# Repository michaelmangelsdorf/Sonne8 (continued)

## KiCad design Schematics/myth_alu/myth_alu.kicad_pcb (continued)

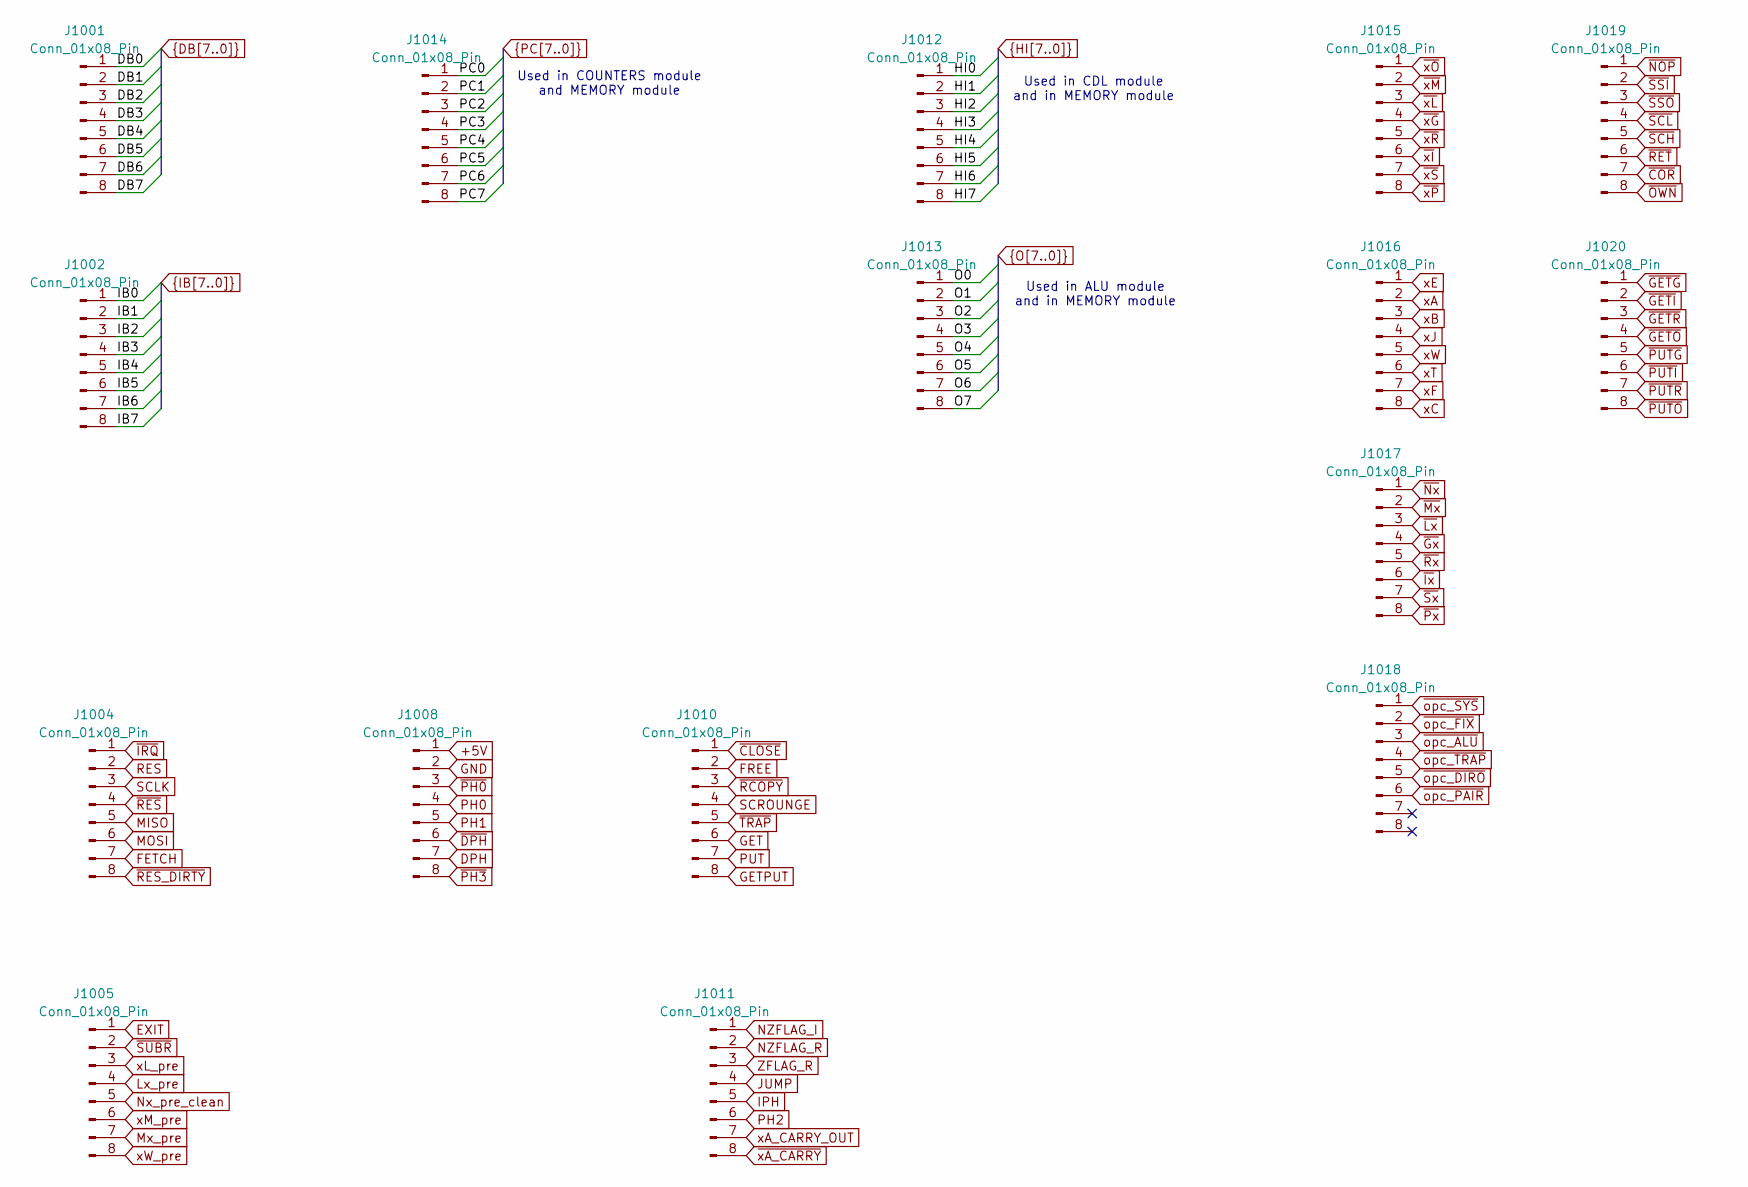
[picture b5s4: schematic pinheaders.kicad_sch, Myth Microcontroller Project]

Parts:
J1001, J1002, J1004, J1005, J1008, J1010, J1011, J1012, J1013, J1014, J1015, J1016, J1017, J1018, J1019, J1020: Conn_01x08_Pin; PinHeader_1x08_P2.54mm_Vertical

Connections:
+5V: J1008.1; also elsewhere on the board
DB0: J1001.1; also elsewhere on the board
DB1: J1001.2; also elsewhere on the board
DB2: J1001.3; also elsewhere on the board
DB3: J1001.4; also elsewhere on the board
DB4: J1001.5; also elsewhere on the board
DB5: J1001.6; also elsewhere on the board
DB6: J1001.7; also elsewhere on the board
DB7: J1001.8; also elsewhere on the board
DPH: J1008.7
EXIT: J1005.1
FETCH: J1004.7
FREE: J1010.2
GET: J1010.6
GETPUT: J1010.8
GND: J1008.2; also elsewhere on the board
HI0: J1012.1
HI1: J1012.2
HI2: J1012.3
HI3: J1012.4
HI4: J1012.5
HI5: J1012.6
HI6: J1012.7
HI7: J1012.8
IB0: J1002.1; also elsewhere on the board
IB1: J1002.2; also elsewhere on the board
IB2: J1002.3; also elsewhere on the board
IB3: J1002.4; also elsewhere on the board
IB4: J1002.5
IB5: J1002.6
IB6: J1002.7
IB7: J1002.8
IPH: J1011.5
JUMP: J1011.4
Lx_pre: J1005.4
MISO: J1004.5
MOSI: J1004.6
Mx_pre: J1005.7
NZFLAG_I: J1011.1
NZFLAG_R: J1011.2; also elsewhere on the board
Nx_pre_clean: J1005.5
O0: J1013.1; also elsewhere on the board
O1: J1013.2; also elsewhere on the board
O2: J1013.3; also elsewhere on the board
O3: J1013.4; also elsewhere on the board
O4: J1013.5; also elsewhere on the board
O5: J1013.6; also elsewhere on the board
O6: J1013.7; also elsewhere on the board
O7: J1013.8; also elsewhere on the board
PC0: J1014.1
PC1: J1014.2
PC2: J1014.3
PC3: J1014.4
PC4: J1014.5
PC5: J1014.6
PC6: J1014.7
PC7: J1014.8
PH0: J1008.4
PH1: J1008.5
PH2: J1011.6
PUT: J1010.7
RES: J1004.2
SCLK: J1004.3
SCROUNGE: J1010.4
ZFLAG_R: J1011.3; also elsewhere on the board
xA: J1016.2; also elsewhere on the board
xA_CARRY_OUT: J1011.7; also elsewhere on the board
xB: J1016.3
xC: J1016.8
xE: J1016.1
xF: J1016.7
xJ: J1016.4
xL_pre: J1005.3
xM_pre: J1005.6
xT: J1016.6
xW: J1016.5
xW_pre: J1005.8
~CLOSE: J1010.1
~COR: J1019.7
~DPH: J1008.6
~Dx: J1017.4
~GETD: J1020.1
~GETI: J1020.2
~GETO: J1020.4
~GETR: J1020.3; also elsewhere on the board
~IRQ: J1004.1
~Ix: J1017.6
~Lx: J1017.3
~Mx: J1017.2
~NOP: J1019.1
~Nx: J1017.1
~OWN: J1019.8
~PH0: J1008.3
~PH3: J1008.8
~PUTD: J1020.5
~PUTI: J1020.6
~PUTO: J1020.8; also elsewhere on the board
~PUTR: J1020.7; also elsewhere on the board
~Px: J1017.8
~RCOPY: J1010.3
~RES_DIRTY: J1004.8
~RES: J1004.4; also elsewhere on the board
~RET: J1019.6
~Rx: J1017.5; also elsewhere on the board
~SCH: J1019.5
~SCL: J1019.4
~SSI: J1019.2
~SSO: J1019.3
~SUBR: J1005.2
~Sx: J1017.7
~TRAP: J1010.5
~opc_ALU: J1018.3; also elsewhere on the board
~opc_DIRO: J1018.5
~opc_FIX: J1018.2; also elsewhere on the board
~opc_PAIR: J1018.6
~opc_SYS: J1018.1
~opc_TRAP: J1018.4
~xA_CARRY: J1011.8
~xD: J1015.4
~xI: J1015.6
~xL: J1015.3
~xM: J1015.2
~xO: J1015.1
~xP: J1015.8
~xR: J1015.5; also elsewhere on the board
~xS: J1015.7

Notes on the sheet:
Used in COUNTERS module and MEMORY module
Used in CDL module and in MEMORY module
Used in ALU module and in MEMORY module

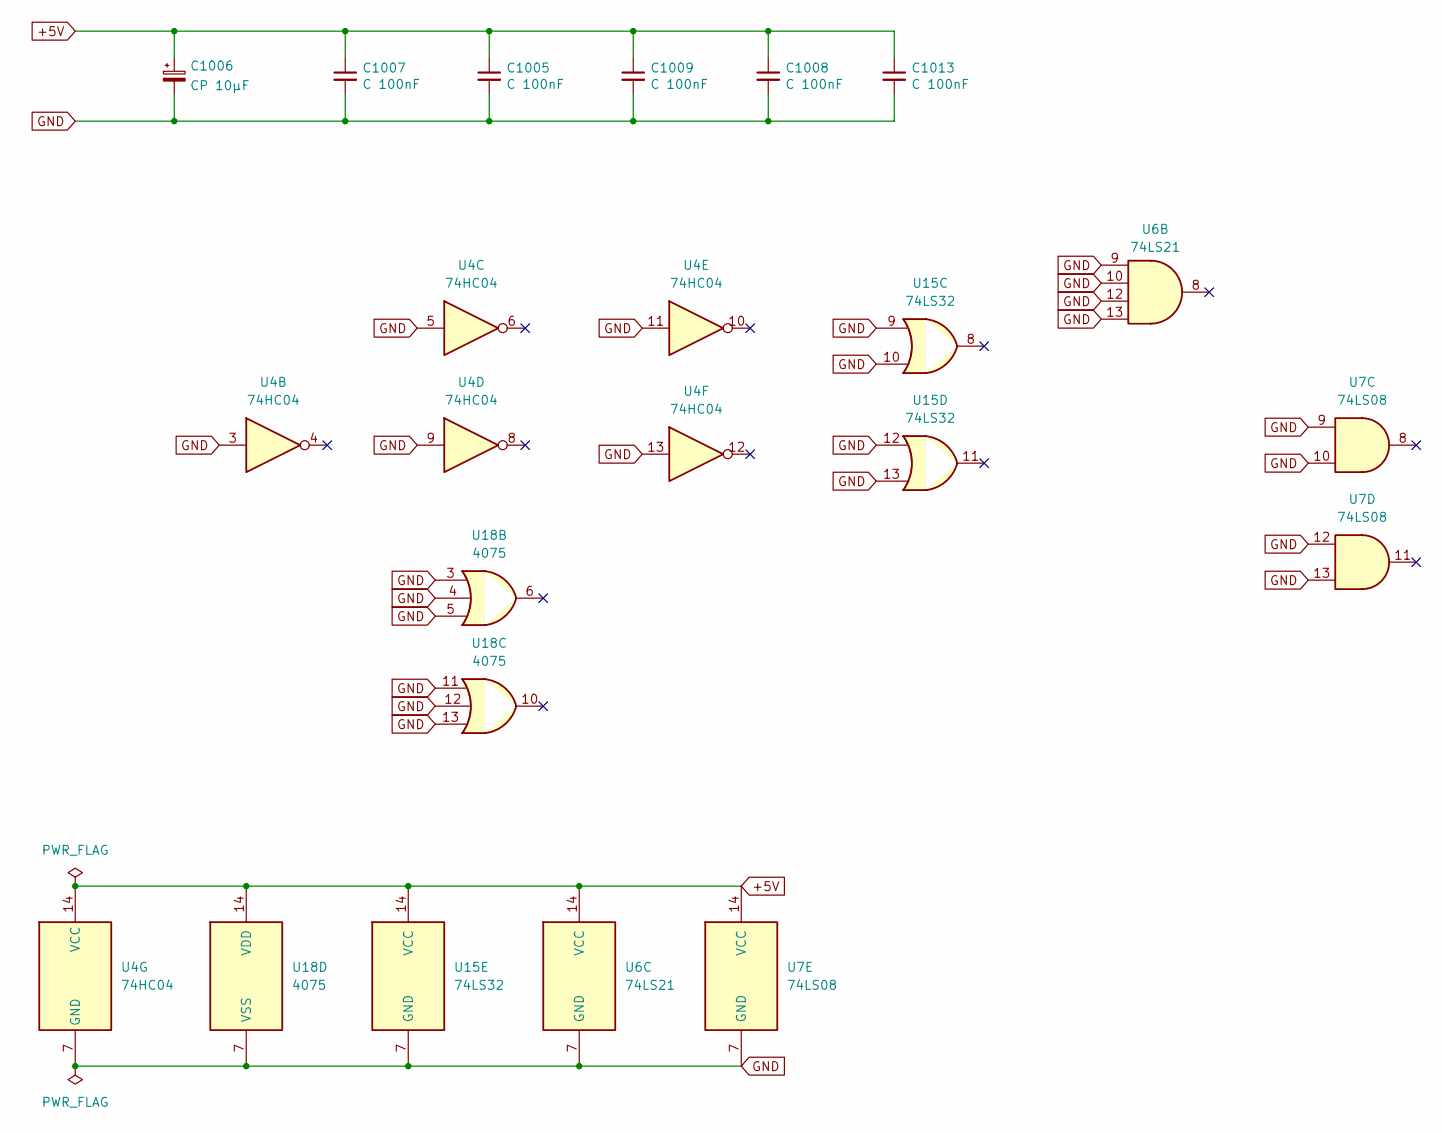
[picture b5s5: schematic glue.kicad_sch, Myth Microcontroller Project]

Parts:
C1005, C1007, C1008, C1009, C1013: C 100nF; C_Disc_D5.0mm_W2.5mm_P2.50mm
C1006: CP 10μF; CP_Radial_D6.3mm_P2.50mm
U4: 74HC04; DIP-14_W7.62mm_Socket_LongPads
U6: 74LS21; DIP-14_W7.62mm_Socket_LongPads
U7: 74LS08; DIP-14_W7.62mm_Socket_LongPads
U15: 74LS32; DIP-14_W7.62mm_Socket_LongPads
U18: 4075; DIP-14_W7.62mm_Socket_LongPads

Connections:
+5V: C1005.1, C1006.1, C1007.1, C1008.1, C1009.1, C1013.1, U4.14 (VCC), U6.14 (VCC), U7.14 (VCC), U15.14 (VCC), U18.14 (VDD); also elsewhere on the board
GND: C1005.2, C1006.2, C1007.2, C1008.2, C1009.2, C1013.2, U4.3, U4.5, U4.7 (GND), U4.9, U4.11, U4.13, U6.7 (GND), U6.9, U6.10, U6.12, U6.13, U7.7 (GND), U7.9, U7.10, U7.12, U7.13, U15.7 (GND), U15.9, U15.10, U15.12, U15.13, U18.3, U18.4, U18.5, U18.7 (VSS), U18.11, U18.12, U18.13; also elsewhere on the board

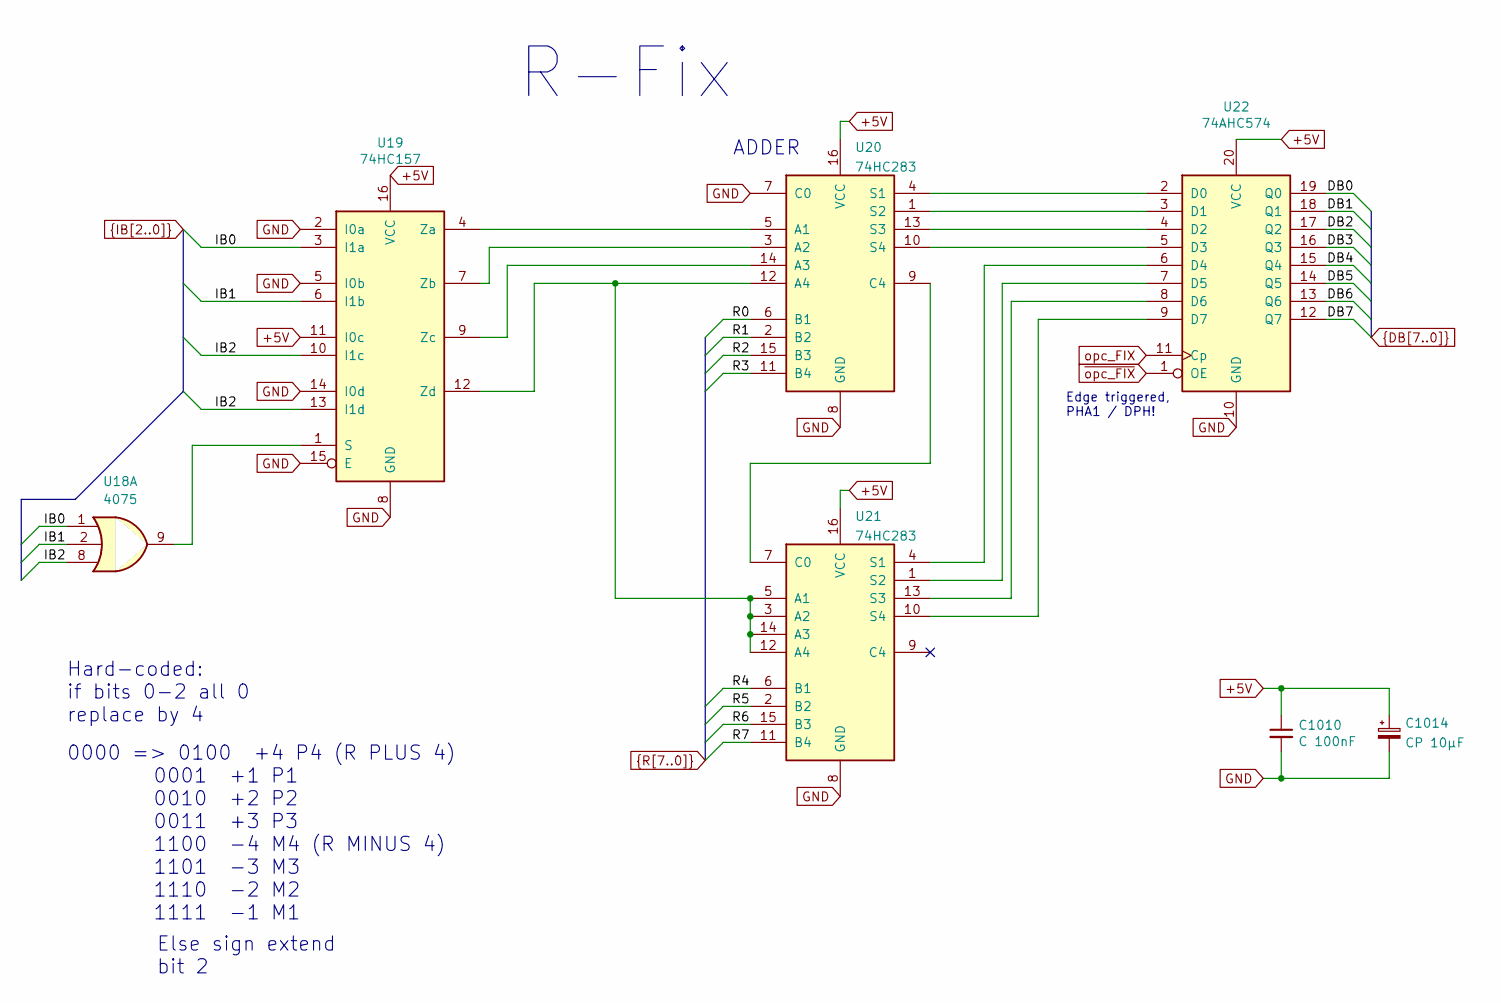
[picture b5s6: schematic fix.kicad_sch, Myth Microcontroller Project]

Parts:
C1010: C 100nF; C_Disc_D5.0mm_W2.5mm_P2.50mm
C1014: CP 10μF; CP_Radial_D6.3mm_P2.50mm
U18: 4075; DIP-14_W7.62mm_Socket_LongPads
U19: 74HC157; DIP-16_W7.62mm_Socket_LongPads
U20, U21: 74HC283; DIP-16_W7.62mm_Socket_LongPads
U22: 74AHC574; DIP-20_W7.62mm_Socket_LongPads

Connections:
+5V: C1010.1, C1014.1, U19.11 (I0c), U19.16 (VCC), U20.16 (VCC), U21.16 (VCC), U22.20 (VCC); also elsewhere on the board
DB0: U22.19 (Q0); also elsewhere on the board
DB1: U22.18 (Q1); also elsewhere on the board
DB2: U22.17 (Q2); also elsewhere on the board
DB3: U22.16 (Q3); also elsewhere on the board
DB4: U22.15 (Q4); also elsewhere on the board
DB5: U22.14 (Q5); also elsewhere on the board
DB6: U22.13 (Q6); also elsewhere on the board
DB7: U22.12 (Q7); also elsewhere on the board
GND: C1010.2, C1014.2, U19.2 (I0a), U19.5 (I0b), U19.8 (GND), U19.14 (I0d), U19.15 (E), U20.7 (C0), U20.8 (GND), U21.8 (GND), U22.10 (GND); also elsewhere on the board
IB0: U18.1, U19.3 (I1a); also elsewhere on the board
IB1: U18.2, U19.6 (I1b); also elsewhere on the board
IB2: U18.8, U19.10 (I1c), U19.13 (I1d); also elsewhere on the board
unnamed: U18.9, U19.1 (S)
unnamed: U19.4 (Za), U20.5 (A1)
unnamed: U19.7 (Zb), U20.3 (A2)
unnamed: U19.9 (Zc), U20.14 (A3)
unnamed: U19.12 (Zd), U20.12 (A4), U21.3 (A2), U21.5 (A1), U21.12 (A4), U21.14 (A3)
unnamed: U20.9 (C4), U21.7 (C0)
unnamed: U20.4 (S1), U22.2 (D0)
unnamed: U20.1 (S2), U22.3 (D1)
unnamed: U20.13 (S3), U22.4 (D2)
unnamed: U20.10 (S4), U22.5 (D3)
unnamed: U21.4 (S1), U22.6 (D4)
unnamed: U21.1 (S2), U22.7 (D5)
unnamed: U21.13 (S3), U22.8 (D6)
unnamed: U21.10 (S4), U22.9 (D7)
R0: U20.6 (B1); also elsewhere on the board
R1: U20.2 (B2); also elsewhere on the board
R2: U20.15 (B3); also elsewhere on the board
R3: U20.11 (B4); also elsewhere on the board
R4: U21.6 (B1); also elsewhere on the board
R5: U21.2 (B2); also elsewhere on the board
R6: U21.15 (B3); also elsewhere on the board
R7: U21.11 (B4); also elsewhere on the board
opc_FIX: U22.11 (Cp)
~opc_FIX: U22.1 (OE); also elsewhere on the board

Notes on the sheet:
ADDER
Edge triggered, PHA1 / DPH!
Else sign extend bit 2
R-Fix
Hard-coded: if bits 0-2 all 0 replace by 4
0000 => 0100 +4 P4 (R PLUS 4) 0001 +1 P1 0010 +2 P2 0011 +3 P3 1100 -4 M4 (R MINUS 4) 1101 -3 M3 1110 -2 M2 1111 -1 M1

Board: 2 copper layers, 52 parts (0 on the bottom side), 96 nets, no tracks yet.

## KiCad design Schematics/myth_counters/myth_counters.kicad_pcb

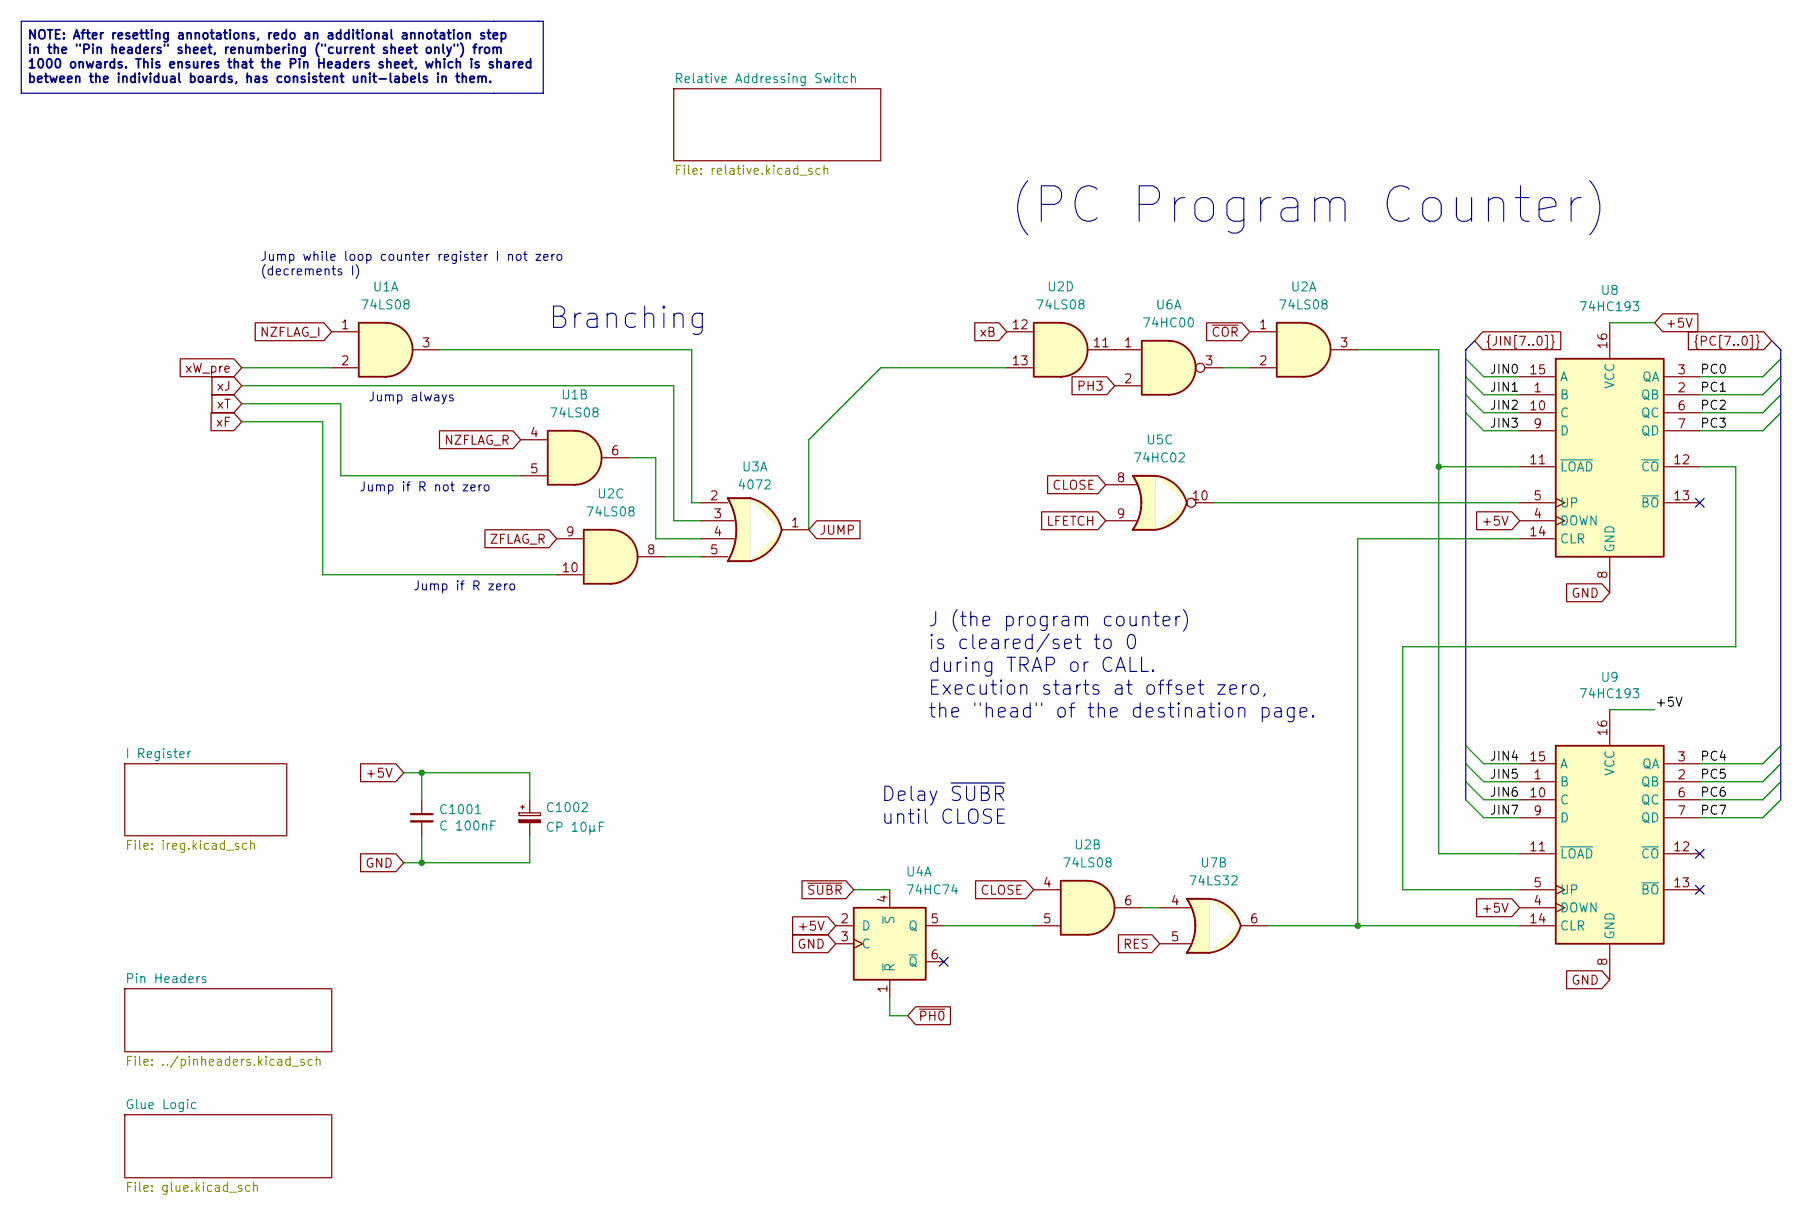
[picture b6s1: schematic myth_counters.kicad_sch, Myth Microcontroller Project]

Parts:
C1001: C 100nF; C_Disc_D5.0mm_W2.5mm_P2.50mm
C1002: CP 10μF; CP_Radial_D6.3mm_P2.50mm
U1, U2: 74LS08; DIP-14_W7.62mm_LongPads
U3: 4072; DIP-14_W7.62mm_LongPads
U4: 74HC74; DIP-14_W7.62mm_LongPads
U5: 74HC02; DIP-14_W7.62mm_LongPads
U6: 74HC00; DIP-14_W7.62mm_LongPads
U7: 74LS32; DIP-14_W7.62mm_LongPads
U8, U9: 74HC193; DIP-16_W7.62mm_Socket_LongPads

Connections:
+5V: C1001.1, C1002.1, U4.2 (D), U8.4 (DOWN), U8.16 (VCC), U9.4 (DOWN), U9.16 (VCC); also elsewhere on the board
CLOSE: U2.4, U5.8
GND: C1001.2, C1002.2, U4.3 (C), U8.8 (GND), U9.8 (GND); also elsewhere on the board
JIN0: U8.15 (A); also elsewhere on the board
JIN1: U8.1 (B); also elsewhere on the board
JIN2: U8.10 (C); also elsewhere on the board
JIN3: U8.9 (D); also elsewhere on the board
JIN4: U9.15 (A); also elsewhere on the board
JIN5: U9.1 (B); also elsewhere on the board
JIN6: U9.10 (C); also elsewhere on the board
JIN7: U9.9 (D); also elsewhere on the board
JUMP: U2.13, U3.1; also elsewhere on the board
LFETCH: U5.9
NZFLAG_I: U1.1; also elsewhere on the board
NZFLAG_R: U1.4; also elsewhere on the board
unnamed: U1.3, U3.2
unnamed: U1.6, U3.4
unnamed: U2.2, U6.3
unnamed: U2.6, U7.4
unnamed: U2.8, U3.5
unnamed: U2.11, U6.1
unnamed: U2.5, U4.5 (Q)
unnamed: U7.6, U8.14 (CLR), U9.14 (CLR)
unnamed: U5.10, U8.5 (UP)
unnamed: U8.12 (~CO), U9.5 (UP)
unnamed: U2.3, U8.11 (~LOAD), U9.11 (~LOAD)
PC0: U8.3 (QA); also elsewhere on the board
PC1: U8.2 (QB); also elsewhere on the board
PC2: U8.6 (QC); also elsewhere on the board
PC3: U8.7 (QD); also elsewhere on the board
PC4: U9.3 (QA); also elsewhere on the board
PC5: U9.2 (QB); also elsewhere on the board
PC6: U9.6 (QC); also elsewhere on the board
PC7: U9.7 (QD); also elsewhere on the board
PH3: U6.2
RES: U7.5; also elsewhere on the board
ZFLAG_R: U2.9; also elsewhere on the board
xB: U2.12; also elsewhere on the board
xF: U2.10; also elsewhere on the board
xJ: U3.3; also elsewhere on the board
xT: U1.5; also elsewhere on the board
xW_pre: U1.2; also elsewhere on the board
~COR: U2.1; also elsewhere on the board
~PH0: U4.1 (~R); also elsewhere on the board
~SUBR: U4.4 (~S); also elsewhere on the board

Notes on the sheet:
Jump always
(PC Program Counter)
Branching
Jump if R zero
J (the program counter) is cleared/set to 0 during TRAP or CALL. Execution starts at offset zero, the "head" of the destination page.
NOTE: After resetting annotations, redo an additional annotation step in the "Pin headers" sheet, renumbering ("current sheet only") from 1000 onwards. This ensures that the Pin Headers sheet, which is shared between the individual boards, has consistent unit-labels in them.
Delay ~{SUBR} until CLOSE
Jump if R not zero
Jump while loop counter register I not zero (decrements I)

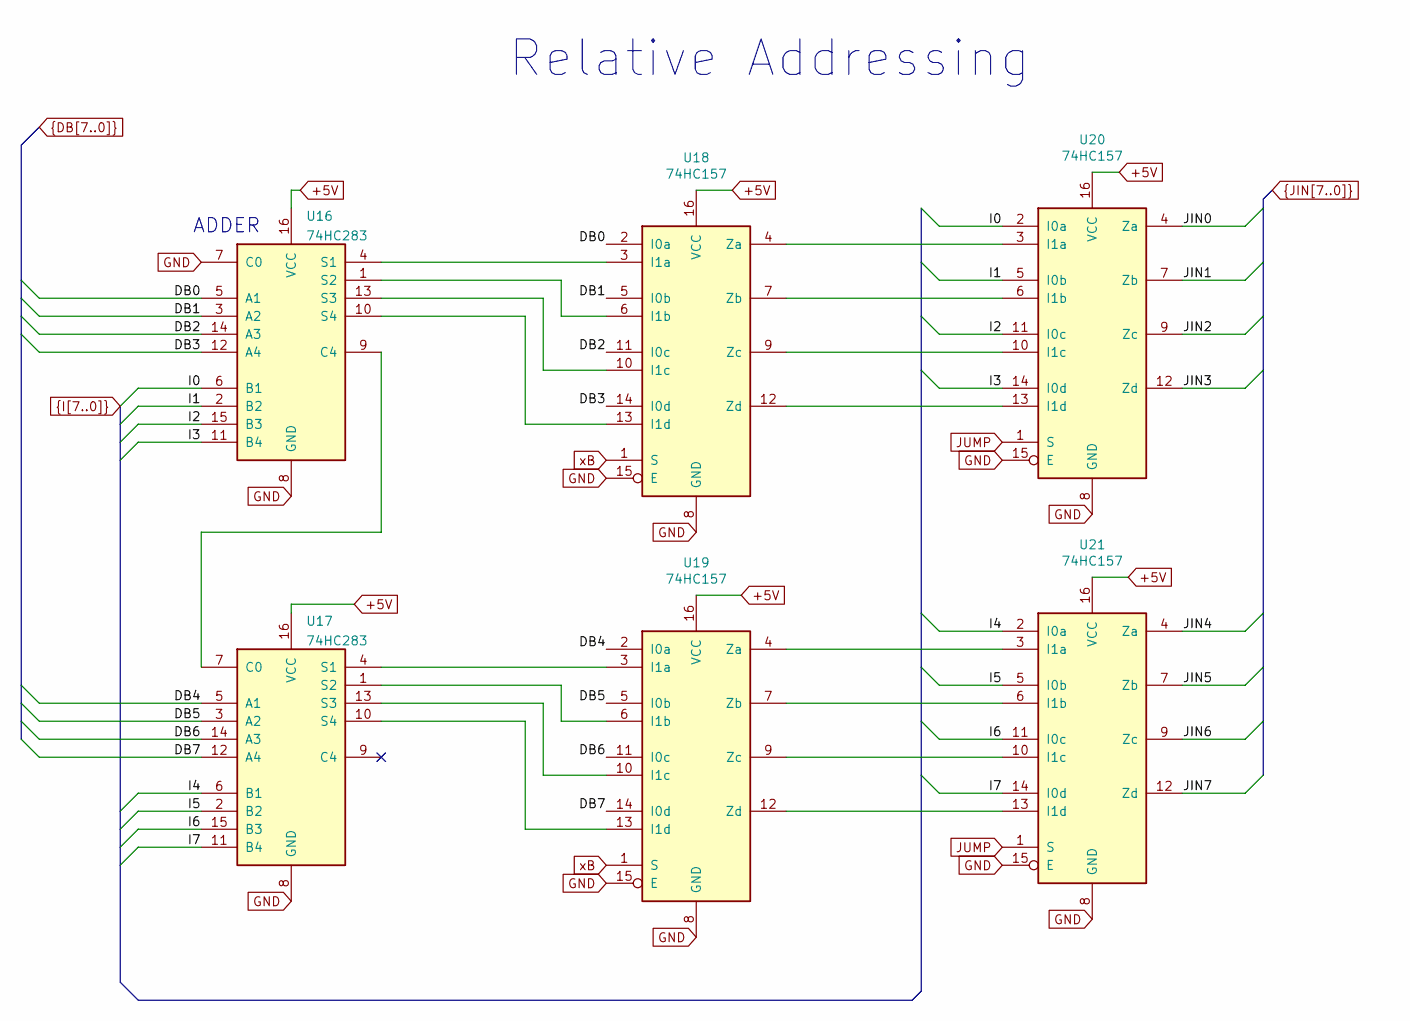
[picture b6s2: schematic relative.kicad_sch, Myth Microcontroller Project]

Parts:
U16, U17: 74HC283; DIP-16_W7.62mm_Socket_LongPads
U18, U19, U20, U21: 74HC157; DIP-16_W7.62mm_Socket_LongPads

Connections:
+5V: U16.16 (VCC), U17.16 (VCC), U18.16 (VCC), U19.16 (VCC), U20.16 (VCC), U21.16 (VCC); also elsewhere on the board
DB0: U16.5 (A1), U18.2 (I0a); also elsewhere on the board
DB1: U16.3 (A2), U18.5 (I0b); also elsewhere on the board
DB2: U16.14 (A3), U18.11 (I0c); also elsewhere on the board
DB3: U16.12 (A4), U18.14 (I0d); also elsewhere on the board
DB4: U17.5 (A1), U19.2 (I0a); also elsewhere on the board
DB5: U17.3 (A2), U19.5 (I0b); also elsewhere on the board
DB6: U17.14 (A3), U19.11 (I0c); also elsewhere on the board
DB7: U17.12 (A4), U19.14 (I0d); also elsewhere on the board
GND: U16.7 (C0), U16.8 (GND), U17.8 (GND), U18.8 (GND), U18.15 (E), U19.8 (GND), U19.15 (E), U20.8 (GND), U20.15 (E), U21.8 (GND), U21.15 (E); also elsewhere on the board
I0: U16.6 (B1), U20.2 (I0a); also elsewhere on the board
I1: U16.2 (B2), U20.5 (I0b); also elsewhere on the board
I2: U16.15 (B3), U20.11 (I0c); also elsewhere on the board
I3: U16.11 (B4), U20.14 (I0d); also elsewhere on the board
I4: U17.6 (B1), U21.2 (I0a); also elsewhere on the board
I5: U17.2 (B2), U21.5 (I0b); also elsewhere on the board
I6: U17.15 (B3), U21.11 (I0c); also elsewhere on the board
I7: U17.11 (B4), U21.14 (I0d); also elsewhere on the board
JIN0: U20.4 (Za); also elsewhere on the board
JIN1: U20.7 (Zb); also elsewhere on the board
JIN2: U20.9 (Zc); also elsewhere on the board
JIN3: U20.12 (Zd); also elsewhere on the board
JIN4: U21.4 (Za); also elsewhere on the board
JIN5: U21.7 (Zb); also elsewhere on the board
JIN6: U21.9 (Zc); also elsewhere on the board
JIN7: U21.12 (Zd); also elsewhere on the board
JUMP: U20.1 (S), U21.1 (S); also elsewhere on the board
unnamed: U16.9 (C4), U17.7 (C0)
unnamed: U16.4 (S1), U18.3 (I1a)
unnamed: U16.1 (S2), U18.6 (I1b)
unnamed: U16.13 (S3), U18.10 (I1c)
unnamed: U16.10 (S4), U18.13 (I1d)
unnamed: U17.4 (S1), U19.3 (I1a)
unnamed: U17.1 (S2), U19.6 (I1b)
unnamed: U17.13 (S3), U19.10 (I1c)
unnamed: U17.10 (S4), U19.13 (I1d)
unnamed: U18.4 (Za), U20.3 (I1a)
unnamed: U18.7 (Zb), U20.6 (I1b)
unnamed: U18.9 (Zc), U20.10 (I1c)
unnamed: U18.12 (Zd), U20.13 (I1d)
unnamed: U19.4 (Za), U21.3 (I1a)
unnamed: U19.7 (Zb), U21.6 (I1b)
unnamed: U19.9 (Zc), U21.10 (I1c)
unnamed: U19.12 (Zd), U21.13 (I1d)
xB: U18.1 (S), U19.1 (S); also elsewhere on the board

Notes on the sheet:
Relative Addressing
ADDER

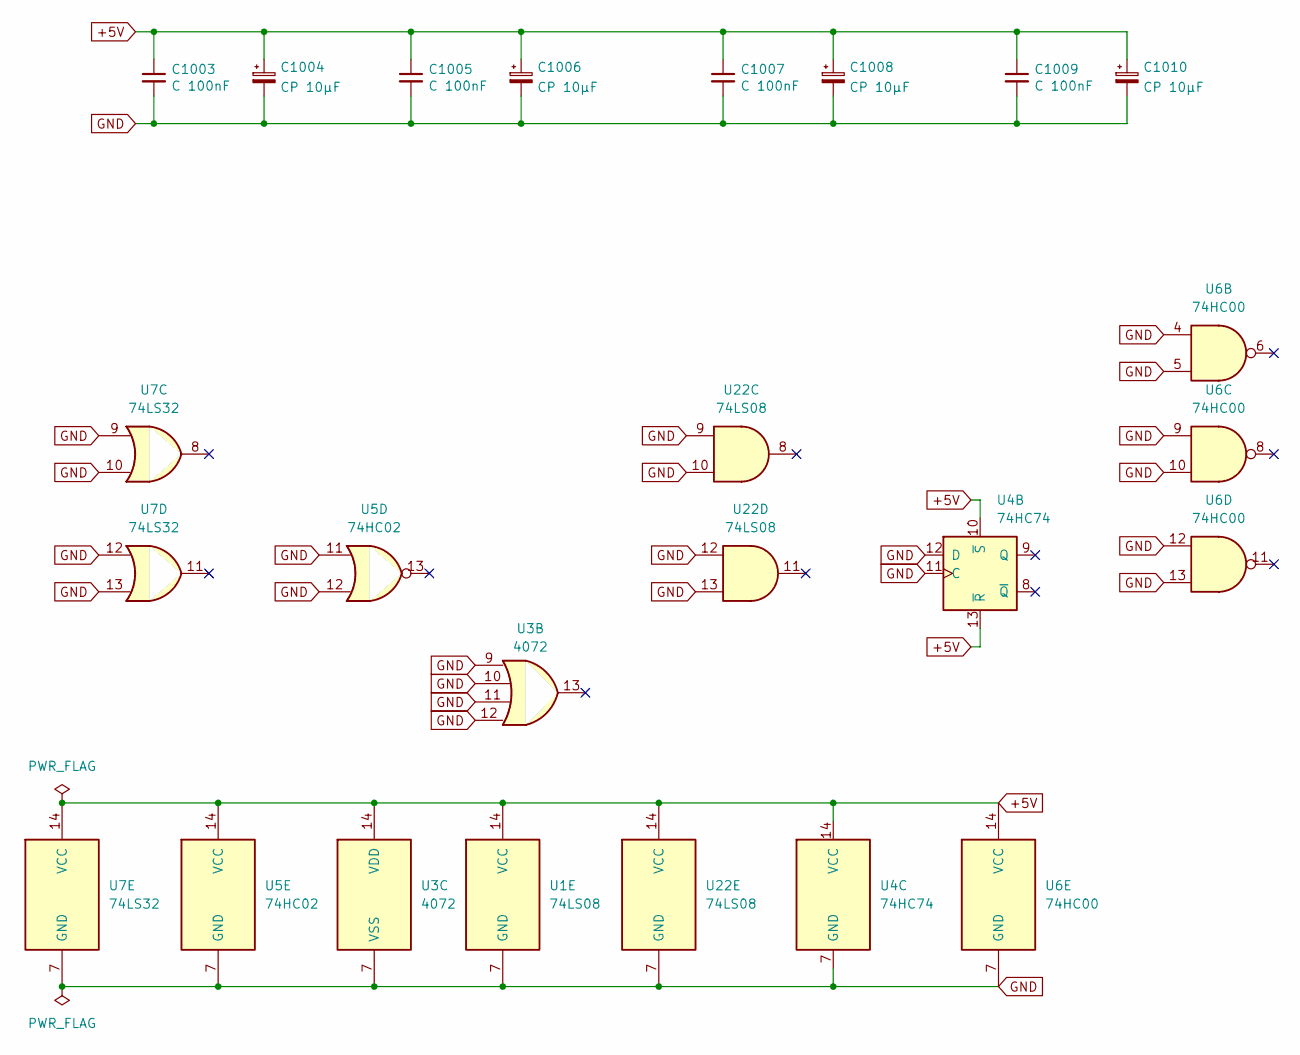
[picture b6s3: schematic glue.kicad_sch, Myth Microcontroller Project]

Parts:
C1003, C1005, C1007, C1009: C 100nF; C_Disc_D5.0mm_W2.5mm_P2.50mm
C1004, C1006, C1008, C1010: CP 10μF; CP_Radial_D6.3mm_P2.50mm
U1, U22: 74LS08; DIP-14_W7.62mm_LongPads
U3: 4072; DIP-14_W7.62mm_LongPads
U4: 74HC74; DIP-14_W7.62mm_LongPads
U5: 74HC02; DIP-14_W7.62mm_LongPads
U6: 74HC00; DIP-14_W7.62mm_LongPads
U7: 74LS32; DIP-14_W7.62mm_LongPads

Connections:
+5V: C1003.1, C1004.1, C1005.1, C1006.1, C1007.1, C1008.1, C1009.1, C1010.1, U1.14 (VCC), U3.14 (VDD), U4.10 (~S), U4.13 (~R), U4.14 (VCC), U5.14 (VCC), U6.14 (VCC), U7.14 (VCC), U22.14 (VCC); also elsewhere on the board
GND: C1003.2, C1004.2, C1005.2, C1006.2, C1007.2, C1008.2, C1009.2, C1010.2, U1.7 (GND), U3.7 (VSS), U3.9, U3.10, U3.11, U3.12, U4.7 (GND), U4.11 (C), U4.12 (D), U5.7 (GND), U5.11, U5.12, U6.4, U6.5, U6.7 (GND), U6.9, U6.10, U6.12, U6.13, U7.7 (GND), U7.9, U7.10, U7.12, U7.13, U22.7 (GND), U22.9, U22.10, U22.12, U22.13; also elsewhere on the board

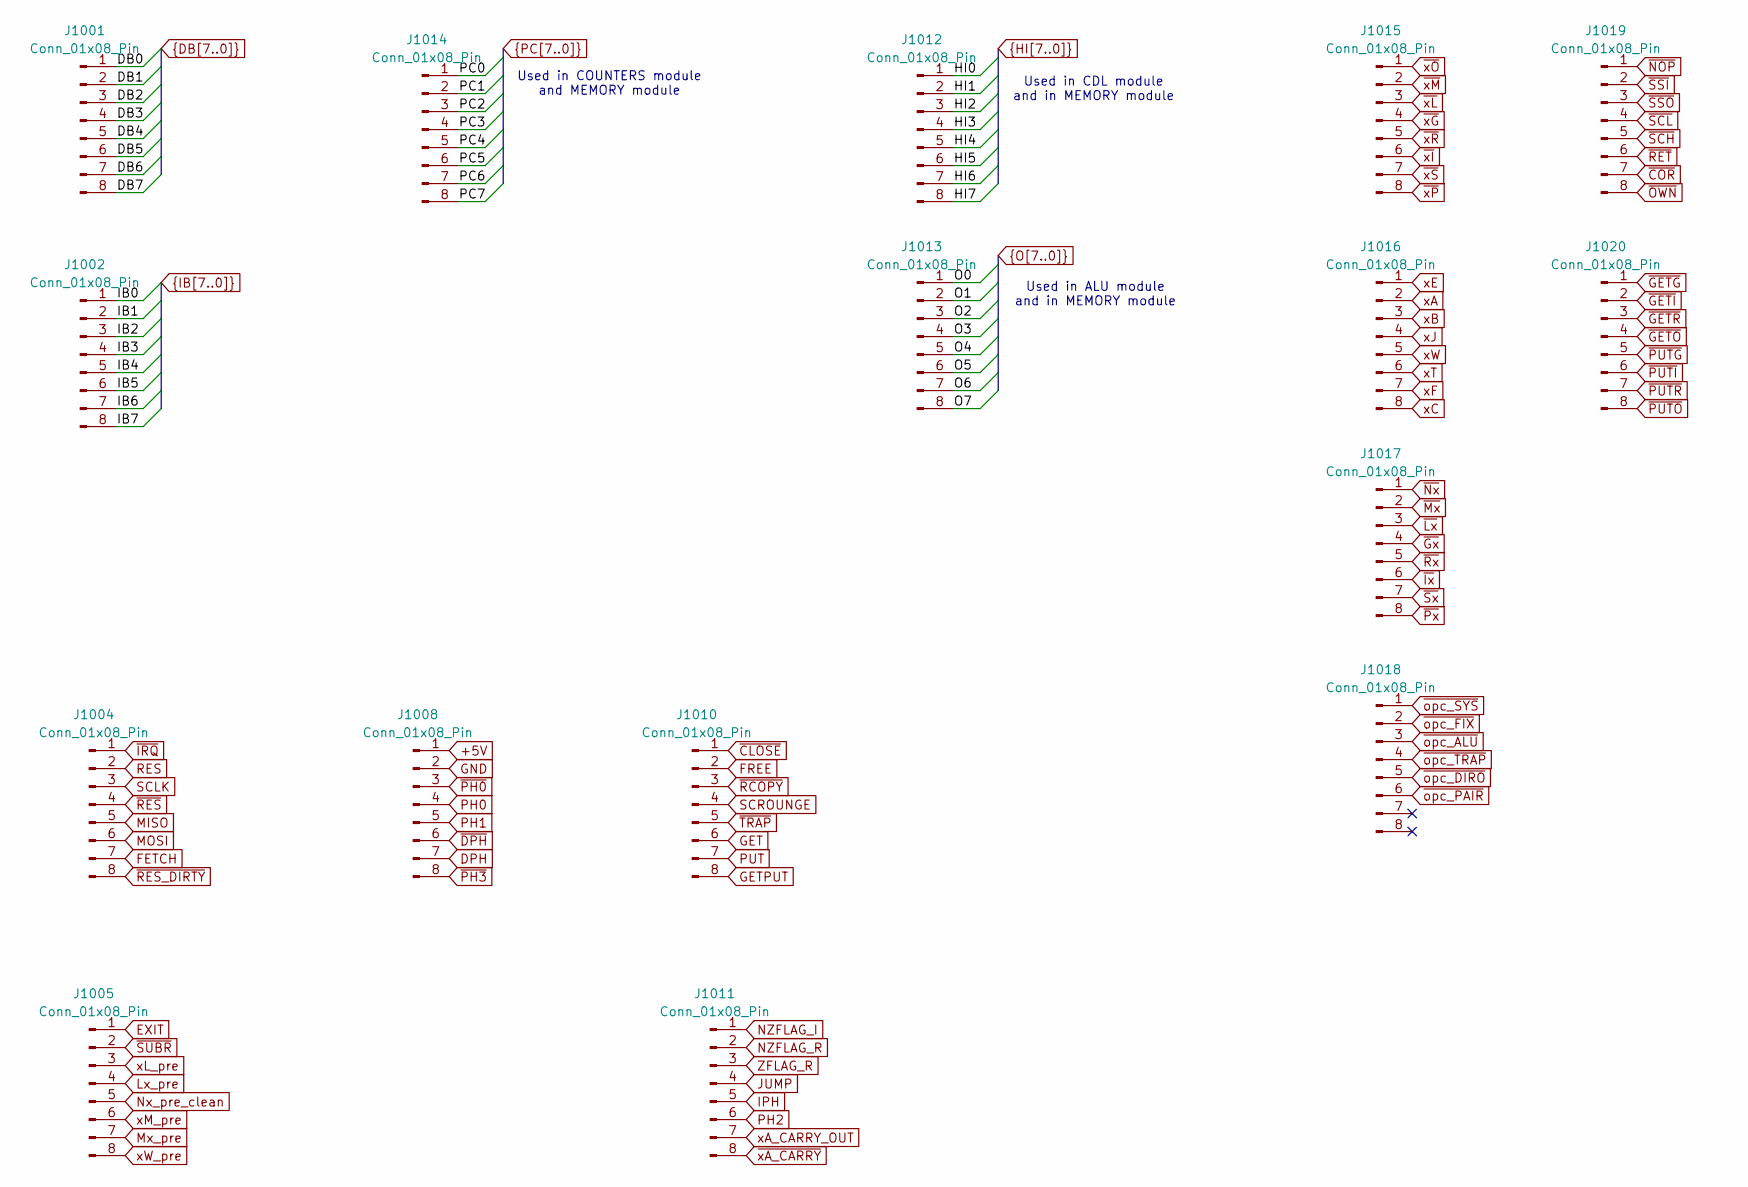
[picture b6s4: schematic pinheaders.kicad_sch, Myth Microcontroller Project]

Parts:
J1001, J1002, J1004, J1005, J1008, J1010, J1011, J1012, J1013, J1014, J1015, J1016, J1017, J1018, J1019, J1020: Conn_01x08_Pin; PinHeader_1x08_P2.54mm_Vertical

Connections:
+5V: J1008.1; also elsewhere on the board
DB0: J1001.1; also elsewhere on the board
DB1: J1001.2; also elsewhere on the board
DB2: J1001.3; also elsewhere on the board
DB3: J1001.4; also elsewhere on the board
DB4: J1001.5; also elsewhere on the board
DB5: J1001.6; also elsewhere on the board
DB6: J1001.7; also elsewhere on the board
DB7: J1001.8; also elsewhere on the board
DPH: J1008.7
EXIT: J1005.1
FETCH: J1004.7
FREE: J1010.2
GET: J1010.6
GETPUT: J1010.8
GND: J1008.2; also elsewhere on the board
HI0: J1012.1
HI1: J1012.2
HI2: J1012.3
HI3: J1012.4
HI4: J1012.5
HI5: J1012.6
HI6: J1012.7
HI7: J1012.8
IB0: J1002.1
IB1: J1002.2
IB2: J1002.3
IB3: J1002.4
IB4: J1002.5
IB5: J1002.6
IB6: J1002.7
IB7: J1002.8
IPH: J1011.5
JUMP: J1011.4; also elsewhere on the board
Lx_pre: J1005.4
MISO: J1004.5
MOSI: J1004.6
Mx_pre: J1005.7
NZFLAG_I: J1011.1; also elsewhere on the board
NZFLAG_R: J1011.2; also elsewhere on the board
Nx_pre_clean: J1005.5
O0: J1013.1
O1: J1013.2
O2: J1013.3
O3: J1013.4
O4: J1013.5
O5: J1013.6
O6: J1013.7
O7: J1013.8
PC0: J1014.1; also elsewhere on the board
PC1: J1014.2; also elsewhere on the board
PC2: J1014.3; also elsewhere on the board
PC3: J1014.4; also elsewhere on the board
PC4: J1014.5; also elsewhere on the board
PC5: J1014.6; also elsewhere on the board
PC6: J1014.7; also elsewhere on the board
PC7: J1014.8; also elsewhere on the board
PH0: J1008.4
PH1: J1008.5
PH2: J1011.6
PUT: J1010.7
RES: J1004.2; also elsewhere on the board
SCLK: J1004.3
SCROUNGE: J1010.4
ZFLAG_R: J1011.3; also elsewhere on the board
xA: J1016.2
xA_CARRY_OUT: J1011.7
xB: J1016.3; also elsewhere on the board
xC: J1016.8
xE: J1016.1
xF: J1016.7; also elsewhere on the board
xJ: J1016.4; also elsewhere on the board
xL_pre: J1005.3
xM_pre: J1005.6
xT: J1016.6; also elsewhere on the board
xW: J1016.5
xW_pre: J1005.8; also elsewhere on the board
~CLOSE: J1010.1
~COR: J1019.7; also elsewhere on the board
~DPH: J1008.6
~Dx: J1017.4
~GETD: J1020.1
~GETI: J1020.2
~GETO: J1020.4
~GETR: J1020.3
~IRQ: J1004.1
~Ix: J1017.6
~Lx: J1017.3
~Mx: J1017.2
~NOP: J1019.1
~Nx: J1017.1
~OWN: J1019.8
~PH0: J1008.3; also elsewhere on the board
~PH3: J1008.8
~PUTD: J1020.5
~PUTI: J1020.6
~PUTO: J1020.8
~PUTR: J1020.7
~Px: J1017.8
~RCOPY: J1010.3
~RES_DIRTY: J1004.8
~RES: J1004.4
~RET: J1019.6
~Rx: J1017.5
~SCH: J1019.5
~SCL: J1019.4
~SSI: J1019.2
~SSO: J1019.3
~SUBR: J1005.2; also elsewhere on the board
~Sx: J1017.7
~TRAP: J1010.5
~opc_ALU: J1018.3
~opc_DIRO: J1018.5
~opc_FIX: J1018.2
~opc_PAIR: J1018.6
~opc_SYS: J1018.1
~opc_TRAP: J1018.4
~xA_CARRY: J1011.8
~xD: J1015.4
~xI: J1015.6
~xL: J1015.3
~xM: J1015.2
~xO: J1015.1
~xP: J1015.8
~xR: J1015.5
~xS: J1015.7

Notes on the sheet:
Used in COUNTERS module and MEMORY module
Used in CDL module and in MEMORY module
Used in ALU module and in MEMORY module
